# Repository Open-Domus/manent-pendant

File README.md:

# Manent pendant: hardware

Hardware design of the Manent pendant: a jewel on a chain that listens for speech around
its wearer, records it, and hands it to the phone over Bluetooth LE. An oval cabochon of
coloured glass in a titanium rim, 40 x 26 mm, whose stone glows while it listens. The stone
and its light come in red, green or blue, chosen at order.
It is the band of `manent-band` in another form: the same circuit, net for net, in a case
made to be looked at. Firmware and radio protocol live in the `mnemo-band` repository.

Public page: [manentlabs.it/en/pendant/](https://manentlabs.it/en/pendant/) (English), [manentlabs.it/pendente/](https://manentlabs.it/pendente/) (Italian).

Nothing here has been built or measured. This is a first design on paper, checked by
scripts, and several of its choices still wait for the project owner.

| What | Where |
| --- | --- |
| Design document: the jewel, requirements, decisions | [docs/design.md](docs/design.md) |
| Does it fit? Case, layers, cell, board area | [docs/space-budget.md](docs/space-budget.md) |
| How long does it last? | [docs/power-budget.md](docs/power-budget.md) |
| What is undecided or unknown, and what would settle it | [docs/open-questions.md](docs/open-questions.md) |
| Parts with sizes and how far each is verified | [parts/parts.yaml](parts/parts.yaml) |
| Circuit, as data | [electrical/gen/design.py](electrical/gen/design.py) |
| Schematic (KiCad 10), PDF, bill of materials | `electrical/kicad/`, `electrical/out/` |
| Board: an ellipse, placed and routed by scripts, not reviewed | `electrical/kicad/pendant.kicad_pcb`, `electrical/out/board-*.svg` |
| Fit model, drawings, STEP | `mechanical/`, `mechanical/out/` |

## Build

Needs `uv`, and either KiCad 10 or Docker (`docker pull kicad/kicad:10.0`).

```
make all        # schematic, board, checks, tests, fit report, drawings, budgets, STEP
make test       # tests only
make route      # draw the tracks again with Freerouting (needs Java and its jar; see tools/route.sh)
```

The schematic and the board are generated: edit `electrical/gen/design.py` and the fit
model, never the `.kicad_sch` or `.kicad_pcb` files.
Every pin carries a label with its net name instead of drawn wires. `make schematic` runs
KiCad's rule check and compares the netlist KiCad reads with the one in `design.py`.

The board is placed and routed by scripts and passes KiCad's checks, but nobody has reviewed
it: see "Board" in the design document before taking it for more than it is. The tracks
are kept in `electrical/kicad/pendant.ses`; when the placement changes, `make route` draws
them again.

## What it shares with the band

The circuit (`electrical/gen/design.py` differs from the band's only in the switch and in
its notes), the pin tables in `parts/pins`, the checks, the power budget's inputs and the
build scripts. A change to the circuit belongs in both repositories.

## Licences

As for the ring and the band: hardware under CERN-OHL-S v2 (`LICENSE`), documents under
CC BY-SA 4.0 (`LICENSE-docs`). The licence of the scripts is not decided.

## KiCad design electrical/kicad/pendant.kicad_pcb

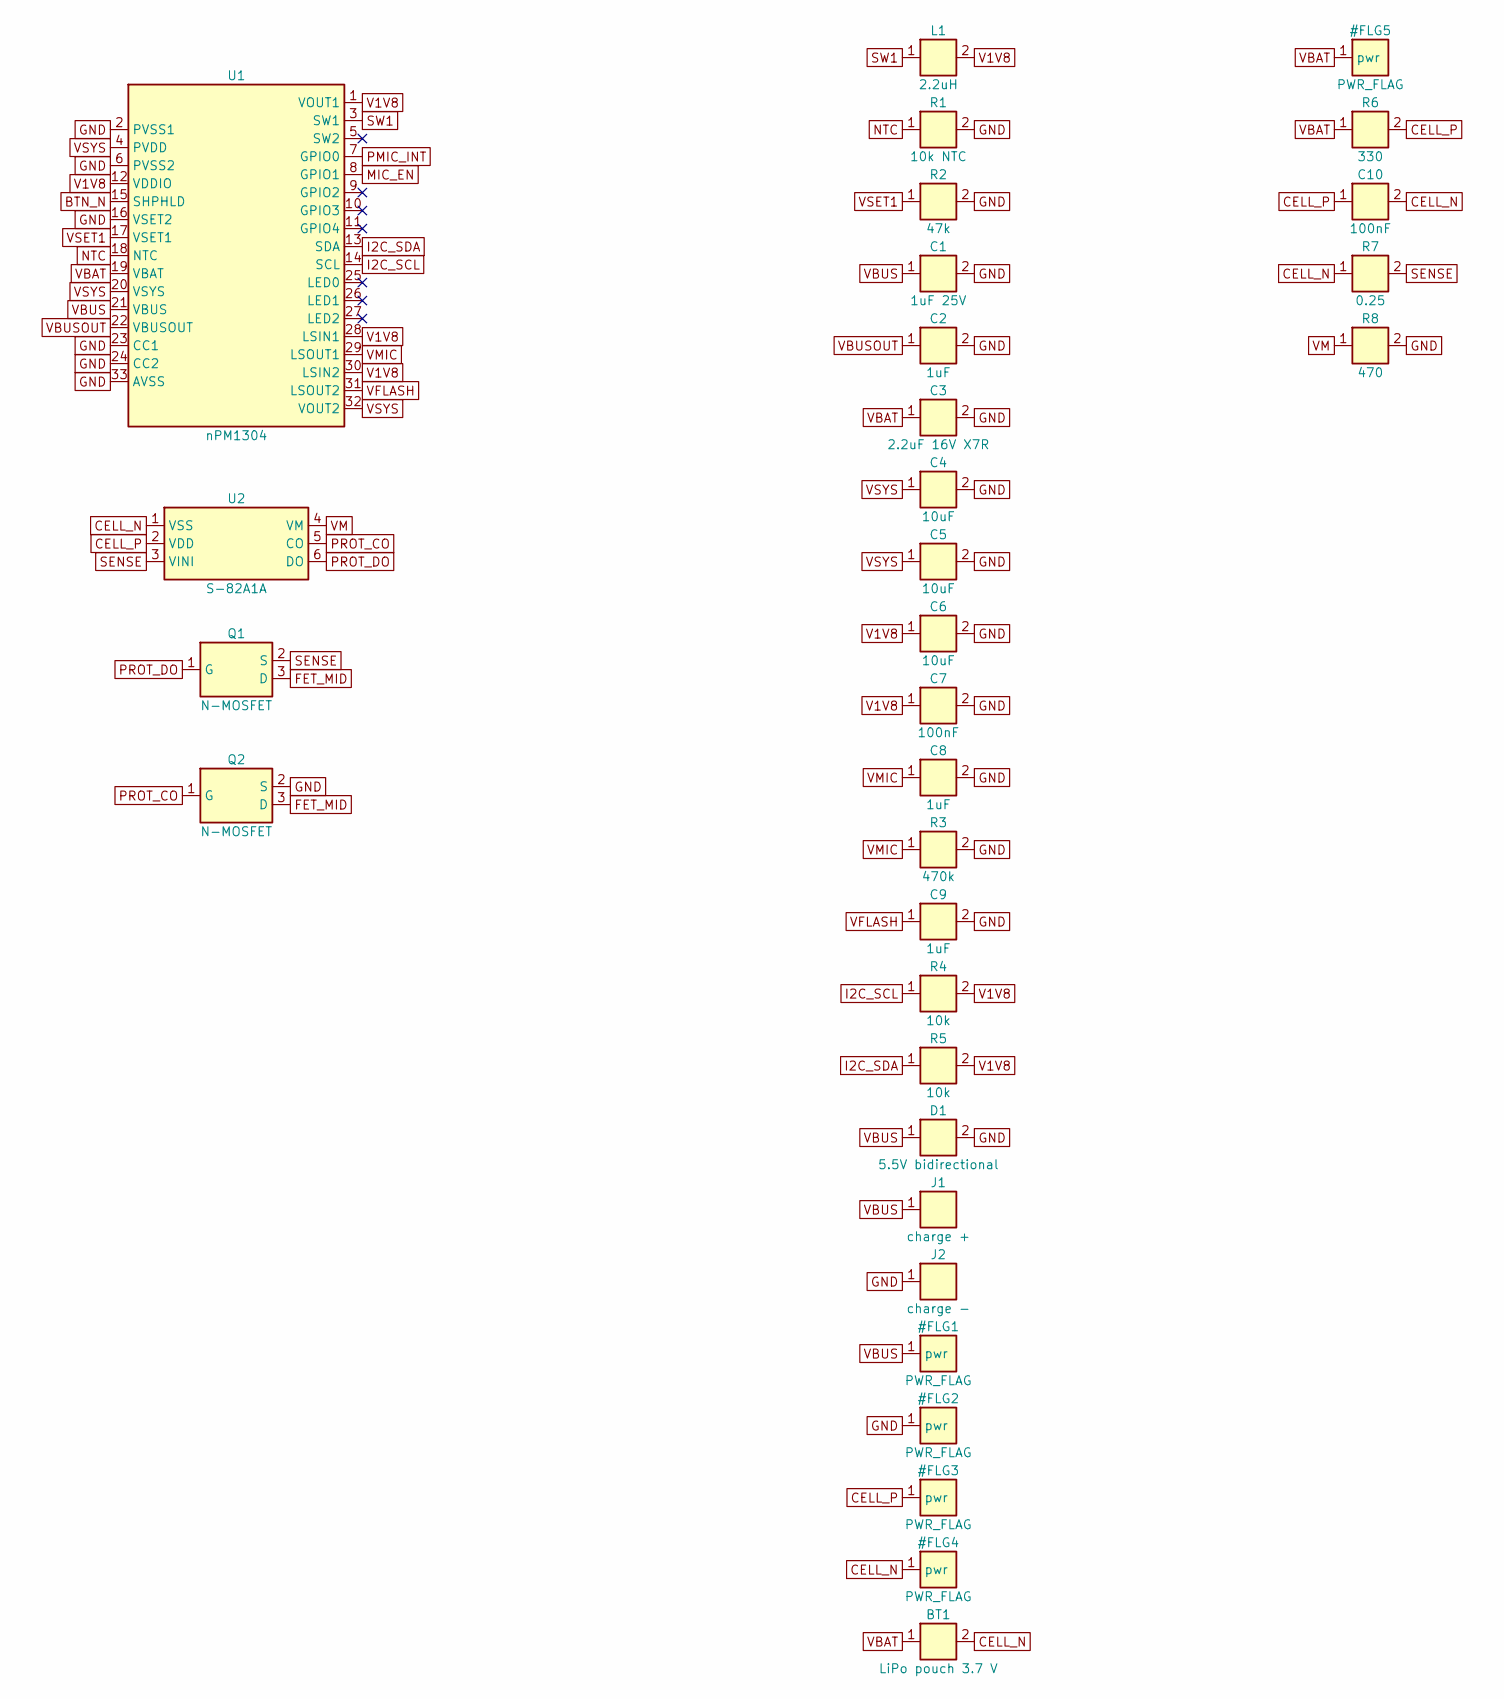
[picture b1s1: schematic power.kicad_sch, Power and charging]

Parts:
BT1: LiPo pouch 3.7 V; Cell_Tabs; MPN 401525 class
C1: 1uF 25V; C_0603_1608Metric
C2, C8, C9: 1uF; C_0402_1005Metric
C3: 2.2uF 16V X7R; C_0603_1608Metric
C4, C5, C6: 10uF; C_0603_1608Metric
C7, C10: 100nF; C_0402_1005Metric
D1: 5.5V bidirectional; D_0201_0603Metric; MPN ESD230-B1-W0201
J1: charge +; Spring_Contact; MPN to choose
J2: charge -; Spring_Contact; MPN to choose
L1: 2.2uH; L_0805_2012Metric; MPN VLS201610HBX-2R2M-1
Q1, Q2: N-MOSFET; SOT-883; MPN PMZB290UNE2
R1: 10k NTC; R_0402_1005Metric; MPN to choose
R2: 47k; R_0402_1005Metric
R3: 470k; R_0402_1005Metric
R4, R5: 10k; R_0402_1005Metric
R6: 330; R_0402_1005Metric
R7: 0.25; R_0402_1005Metric
R8: 470; R_0402_1005Metric
U1: nPM1304; QFN-32-1EP_5x5mm_P0.5mm_EP3.45x3.45mm; MPN nPM1304-QEAA-R7
U2: S-82A1A; DFN-6_1414; MPN S-82A1AAG-A6T5S (variant to confirm)

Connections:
BTN_N: U1.15 (SHPHLD); also elsewhere on the board
CELL_N: BT1.2, C10.2, R7.1, U2.1 (VSS)
CELL_P: C10.1, R6.2, U2.2 (VDD)
FET_MID: Q1.3 (D), Q2.3 (D)
GND: C1.2, C2.2, C3.2, C4.2, C5.2, C6.2, C7.2, C8.2, C9.2, D1.2, J2.1, Q2.2 (S), R1.2, R2.2, R3.2, R8.2, U1.2 (PVSS1), U1.6 (PVSS2), U1.16 (VSET2), U1.23 (CC1), U1.24 (CC2), U1.33 (AVSS); also elsewhere on the board
I2C_SCL: R4.1, U1.14 (SCL); also elsewhere on the board
I2C_SDA: R5.1, U1.13 (SDA); also elsewhere on the board
MIC_EN: U1.8 (GPIO1); also elsewhere on the board
NTC: R1.1, U1.18 (NTC)
PMIC_INT: U1.7 (GPIO0); also elsewhere on the board
PROT_CO: Q2.1 (G), U2.5 (CO)
PROT_DO: Q1.1 (G), U2.6 (DO)
SENSE: Q1.2 (S), R7.2, U2.3 (VINI)
SW1: L1.1, U1.3 (SW1)
V1V8: C6.1, C7.1, L1.2, R4.2, R5.2, U1.1 (VOUT1), U1.12 (VDDIO), U1.28 (LSIN1), U1.30 (LSIN2); also elsewhere on the board
VBAT: BT1.1, C3.1, R6.1, U1.19 (VBAT); also elsewhere on the board
VBUS: C1.1, D1.1, J1.1, U1.21 (VBUS); also elsewhere on the board
VBUSOUT: C2.1, U1.22 (VBUSOUT)
VFLASH: C9.1, U1.31 (LSOUT2); also elsewhere on the board
VM: R8.1, U2.4 (VM)
VMIC: C8.1, R3.1, U1.29 (LSOUT1); also elsewhere on the board
VSET1: R2.1, U1.17 (VSET1)
VSYS: C4.1, C5.1, U1.4 (PVDD), U1.20 (VSYS), U1.32 (VOUT2); also elsewhere on the board

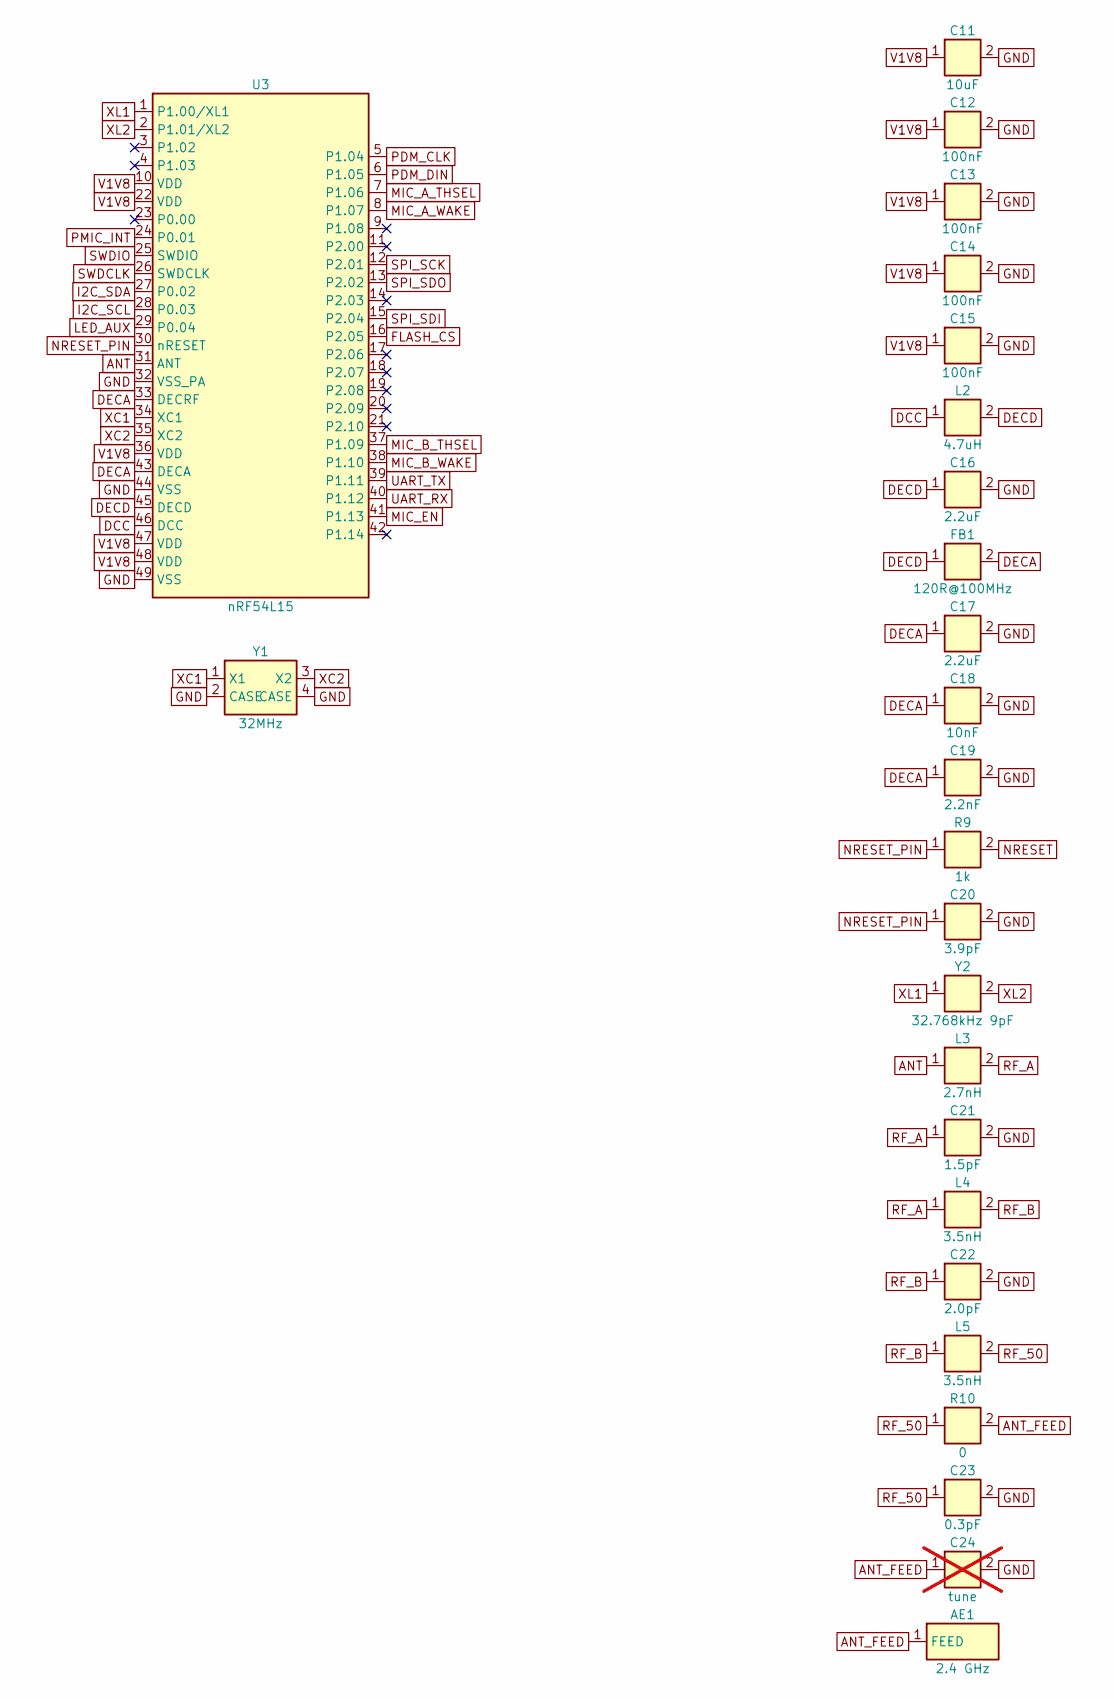
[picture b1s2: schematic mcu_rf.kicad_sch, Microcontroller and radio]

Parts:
AE1: 2.4 GHz; Antenna_1608; MPN ANT1608LL14R2400A
C11: 10uF; C_0603_1608Metric
C12, C13, C14, C15: 100nF; C_0201_0603Metric
C16, C17: 2.2uF; C_0201_0603Metric
C18: 10nF; C_0201_0603Metric
C19: 2.2nF; C_0201_0603Metric
C20: 3.9pF; C_0201_0603Metric
C21: 1.5pF; C_0201_0603Metric; MPN GJM0335C1E1R5WB01
C22: 2.0pF; C_0201_0603Metric; MPN GJM0335C1E2R0WB01
C23: 0.3pF; C_0201_0603Metric
C24: tune; C_0201_0603Metric; not fitted
FB1: 120R@100MHz; L_0201_0603Metric; MPN BLM03AG121SN1D
L2: 4.7uH; L_0402_1005Metric; MPN PLEA67BCA4R7M-1PT00
L3: 2.7nH; L_0201_0603Metric; MPN LQP03HQ2N7B02
L4, L5: 3.5nH; L_0201_0603Metric; MPN LQP03HQ3N5B02
R9: 1k; R_0201_0603Metric
R10: 0; R_0201_0603Metric
U3: nRF54L15; QFN-48-1EP_6x6mm_P0.4mm_EP4.6x4.6mm; MPN nRF54L15-QFAA-R
Y1: 32MHz; Crystal_SMD_2016-4Pin_2.0x1.6mm; MPN CX2016DB32000D0FLJCC
Y2: 32.768kHz 9pF; Crystal_SMD_2012-2Pin_2.0x1.2mm; MPN 9HT11-32.768KDZC-T

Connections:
ANT: L3.1, U3.31 (ANT)
ANT_FEED: AE1.1, C24.1, R10.2
DCC: L2.1, U3.46 (DCC)
DECA: C17.1, C18.1, C19.1, FB1.2, U3.33 (DECRF), U3.43 (DECA)
DECD: C16.1, FB1.1, L2.2, U3.45 (DECD)
FLASH_CS: U3.16 (P2.05); also elsewhere on the board
GND: C11.2, C12.2, C13.2, C14.2, C15.2, C16.2, C17.2, C18.2, C19.2, C20.2, C21.2, C22.2, C23.2, C24.2, U3.32 (VSS_PA), U3.44 (VSS), U3.49 (VSS), Y1.2 (CASE), Y1.4 (CASE); also elsewhere on the board
I2C_SCL: U3.28 (P0.03); also elsewhere on the board
I2C_SDA: U3.27 (P0.02); also elsewhere on the board
LED_AUX: U3.29 (P0.04); also elsewhere on the board
MIC_A_THSEL: U3.7 (P1.06); also elsewhere on the board
MIC_A_WAKE: U3.8 (P1.07); also elsewhere on the board
MIC_B_THSEL: U3.37 (P1.09); also elsewhere on the board
MIC_B_WAKE: U3.38 (P1.10); also elsewhere on the board
MIC_EN: U3.41 (P1.13); also elsewhere on the board
NRESET: R9.2; also elsewhere on the board
NRESET_PIN: C20.1, R9.1, U3.30 (nRESET)
PDM_CLK: U3.5 (P1.04); also elsewhere on the board
PDM_DIN: U3.6 (P1.05); also elsewhere on the board
PMIC_INT: U3.24 (P0.01); also elsewhere on the board
RF_50: C23.1, L5.2, R10.1
RF_A: C21.1, L3.2, L4.1
RF_B: C22.1, L4.2, L5.1
SPI_SCK: U3.12 (P2.01); also elsewhere on the board
SPI_SDI: U3.15 (P2.04); also elsewhere on the board
SPI_SDO: U3.13 (P2.02); also elsewhere on the board
SWDCLK: U3.26 (SWDCLK); also elsewhere on the board
SWDIO: U3.25 (SWDIO); also elsewhere on the board
UART_RX: U3.40 (P1.12); also elsewhere on the board
UART_TX: U3.39 (P1.11); also elsewhere on the board
V1V8: C11.1, C12.1, C13.1, C14.1, C15.1, U3.10 (VDD), U3.22 (VDD), U3.36 (VDD), U3.47 (VDD), U3.48 (VDD); also elsewhere on the board
XC1: U3.34 (XC1), Y1.1 (X1)
XC2: U3.35 (XC2), Y1.3 (X2)
XL1: U3.1 (P1.00/XL1), Y2.1
XL2: U3.2 (P1.01/XL2), Y2.2

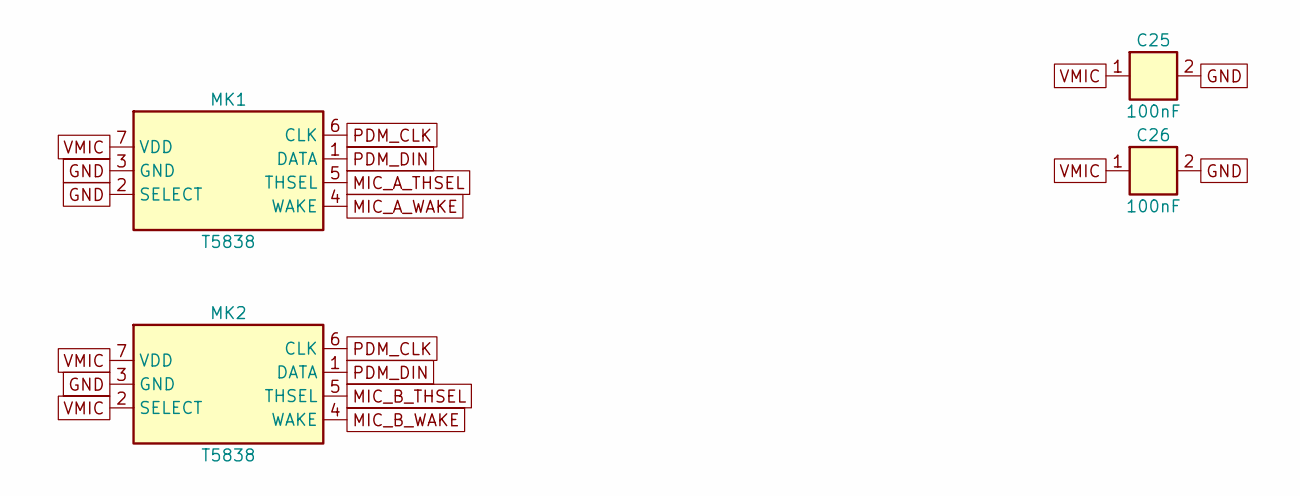
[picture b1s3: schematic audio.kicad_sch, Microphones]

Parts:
C25, C26: 100nF; C_0201_0603Metric
MK1, MK2: T5838; MPN MMICT5838-00-012

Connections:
GND: C25.2, C26.2, MK1.2 (SELECT), MK1.3 (GND), MK2.3 (GND); also elsewhere on the board
MIC_A_THSEL: MK1.5 (THSEL); also elsewhere on the board
MIC_A_WAKE: MK1.4 (WAKE); also elsewhere on the board
MIC_B_THSEL: MK2.5 (THSEL); also elsewhere on the board
MIC_B_WAKE: MK2.4 (WAKE); also elsewhere on the board
PDM_CLK: MK1.6 (CLK), MK2.6 (CLK); also elsewhere on the board
PDM_DIN: MK1.1 (DATA), MK2.1 (DATA); also elsewhere on the board
VMIC: C25.1, C26.1, MK1.7 (VDD), MK2.2 (SELECT), MK2.7 (VDD); also elsewhere on the board

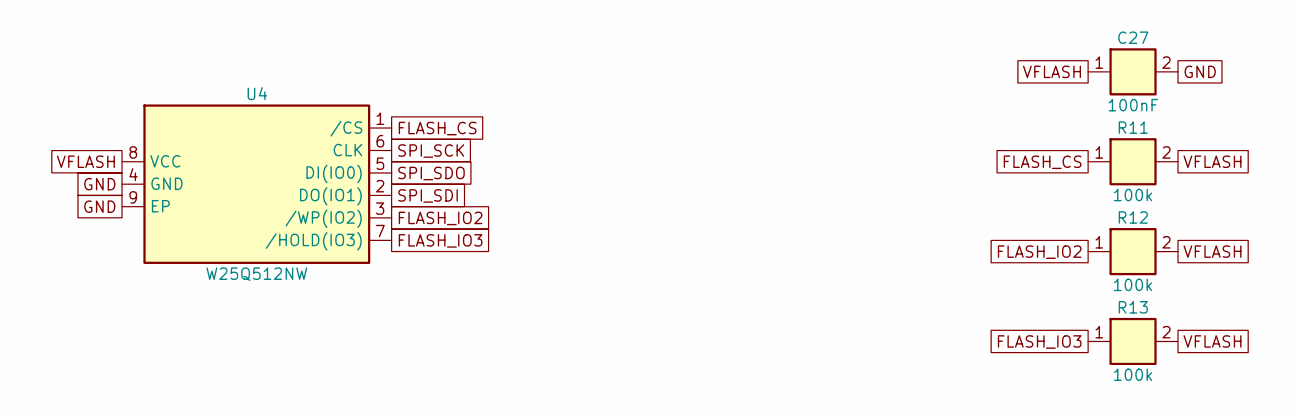
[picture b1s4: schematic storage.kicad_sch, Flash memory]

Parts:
C27: 100nF; C_0402_1005Metric
R11, R12, R13: 100k; R_0402_1005Metric
U4: W25Q512NW; WSON-8-1EP_8x6mm_P1.27mm_EP3.4x4.3mm; MPN W25Q512NW (ordering code to confirm)

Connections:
FLASH_CS: R11.1, U4.1 (/CS); also elsewhere on the board
FLASH_IO2: R12.1, U4.3 (/WP(IO2))
FLASH_IO3: R13.1, U4.7 (/HOLD(IO3))
GND: C27.2, U4.4 (GND), U4.9 (EP); also elsewhere on the board
SPI_SCK: U4.6 (CLK); also elsewhere on the board
SPI_SDI: U4.2 (DO(IO1)); also elsewhere on the board
SPI_SDO: U4.5 (DI(IO0)); also elsewhere on the board
VFLASH: C27.1, R11.2, R12.2, R13.2, U4.8 (VCC); also elsewhere on the board

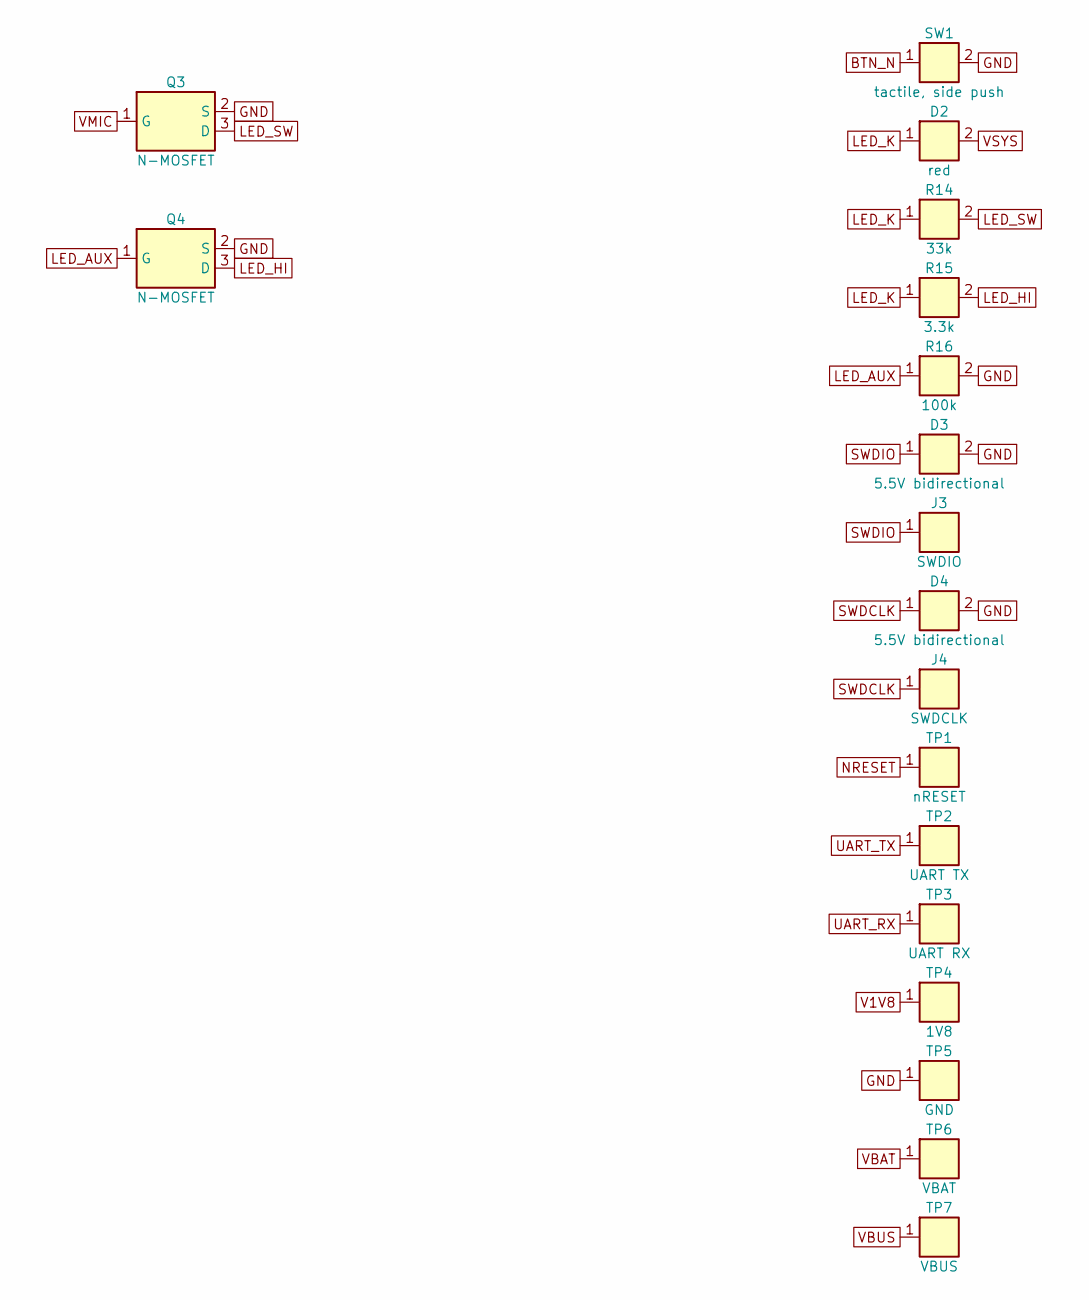
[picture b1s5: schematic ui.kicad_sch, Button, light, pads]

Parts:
D2: red; LED_0402_1005Metric; MPN SML-P11VT
D3, D4: 5.5V bidirectional; D_0201_0603Metric; MPN ESD230-B1-W0201
J3: SWDIO; Spring_Contact; MPN to choose
J4: SWDCLK; Spring_Contact; MPN to choose
Q3, Q4: N-MOSFET; SOT-883; MPN PMZB290UNE2
R14: 33k; R_0402_1005Metric
R15: 3.3k; R_0402_1005Metric
R16: 100k; R_0402_1005Metric
SW1: tactile, side push; EVQP7J; MPN EVQP7J01P
TP1: nRESET; Pad_Test_D1.0
TP2: UART TX; Pad_Test_D1.0
TP3: UART RX; Pad_Test_D1.0
TP4: 1V8; Pad_Test_D1.0
TP5: GND; Pad_Test_D1.0
TP6: VBAT; Pad_Test_D1.0
TP7: VBUS; Pad_Test_D1.0

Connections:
BTN_N: SW1.1; also elsewhere on the board
GND: D3.2, D4.2, Q3.2 (S), Q4.2 (S), R16.2, SW1.2, TP5.1; also elsewhere on the board
LED_AUX: Q4.1 (G), R16.1; also elsewhere on the board
LED_HI: Q4.3 (D), R15.2
LED_K: D2.1, R14.1, R15.1
LED_SW: Q3.3 (D), R14.2
NRESET: TP1.1; also elsewhere on the board
SWDCLK: D4.1, J4.1; also elsewhere on the board
SWDIO: D3.1, J3.1; also elsewhere on the board
UART_RX: TP3.1; also elsewhere on the board
UART_TX: TP2.1; also elsewhere on the board
V1V8: TP4.1; also elsewhere on the board
VBAT: TP6.1; also elsewhere on the board
VBUS: TP7.1; also elsewhere on the board
VMIC: Q3.1 (G); also elsewhere on the board
VSYS: D2.2; also elsewhere on the board

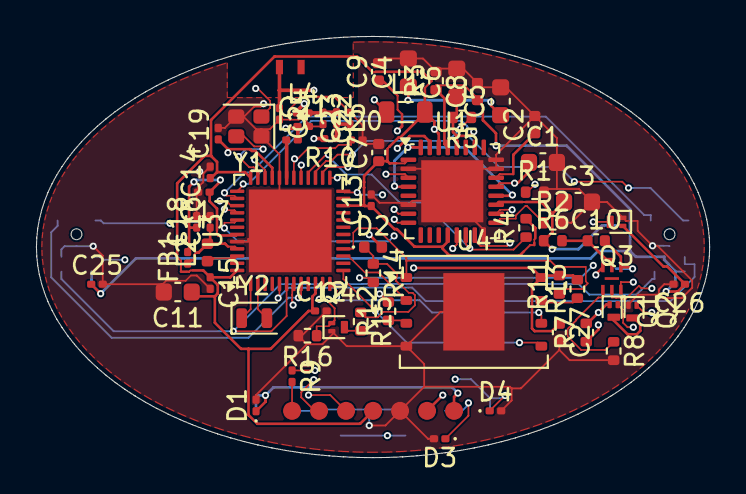
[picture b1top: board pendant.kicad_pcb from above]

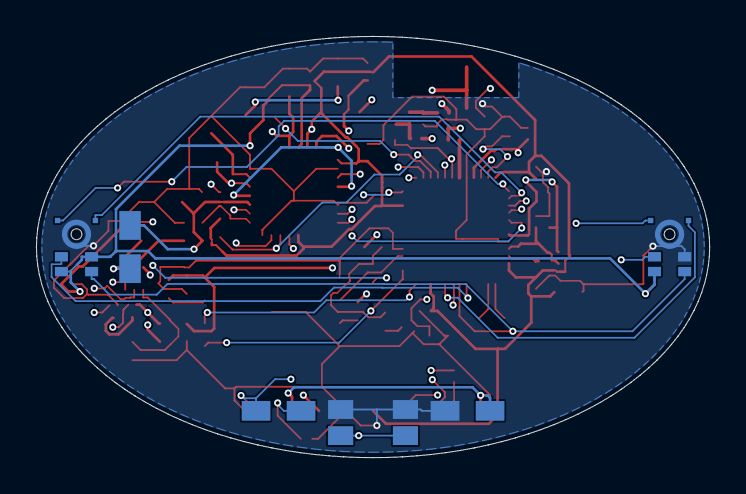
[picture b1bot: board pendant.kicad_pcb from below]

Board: 4 copper layers, 37.4 x 23.4 mm, 79 parts (8 on the bottom side), 57 nets.

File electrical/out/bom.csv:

References,Quantity,Value,Manufacturer,Part number,Package,Fitted,Notes
U1,1,nPM1304,Nordic Semiconductor,nPM1304-QEAA-R7,"QFN-32 5x5, 0.5 mm pitch",yes,"Charges at up to 100 mA: enough for these cells. BUCK2 unused as in Nordic's reference configuration 2: VSET2 grounded, SW2 open, VOUT2 to VSYS. LED0-2, GPIO2-4 left open"
L1,1,2.2uH,TDK,VLS201610HBX-2R2M-1,0806,yes,"Nordic asks for DCR under 0.4 ohm in 0806 (2.0 x 1.6 mm); this one is 0.17 max, 1.45 A, 1.0 tall. The same part on the band, the card and the pendant"
R1,1,10k NTC,,to choose,0402,yes,"Thermistor, B about 3380 K, against the cell: stops the charge when the closed case is too warm or too cold"
R2,1,47k,,,0402,yes,Sets BUCK1 to 1.8 V at power-on
C1,1,1uF 25V,,,0603,yes,"As Nordic's nPM1304-QEAA reference layout 1.0, configuration 2"
C2 C8 C9,3,1uF,,,0402,yes,"As Nordic's nPM1304-QEAA reference layout 1.0, configuration 2 | Load switch output. As Nordic's nPM1304-QEAA reference layout 1.0, configuration 2"
C3,1,2.2uF 16V X7R,,,0603,yes,"As Nordic's nPM1304-QEAA reference layout 1.0, configuration 2 (Taiyo Yuden EMK107BB7225KA-T there)"
C4 C5 C6 C11,4,10uF,,,0603,yes,"Buck input, at PVDD and PVSS1. As Nordic's nPM1304-QEAA reference layout 1.0, configuration 2 | VSYS output. As Nordic's nPM1304-QEAA reference layout 1.0, configuration 2 | Buck output: at least 4 uF effective. As Nordic's nPM1304-QEAA reference layout 1.0, configuration 2"
C7 C10 C27,3,100nF,,,0402,yes,VDDIO
R3,1,470k,,,0402,yes,"Empties the rail when the load switch opens, so a mute puts the light out at once, as on the ring and the card"
R4 R5,2,10k,,,0402,yes,
D1 D3 D4,3,5.5V bidirectional,Infineon,ESD230-B1-W0201,0201,yes,"The pad is on the outside of the closed case, against the skin: protected as on the card"
J1,1,charge +,,to choose,spring contact,yes,To a pad on the back cover. The bail lets the pendant into its dock one way only
J2,1,charge -,,to choose,spring contact,yes,
BT1,1,LiPo pouch 3.7 V,to choose,401525 class,,yes,Size and capacity depend on the case; see docs/space-budget.md
R6,1,330,,,0402,yes,Protector supply filter
U2,1,S-82A1A,ABLIC,S-82A1AAG-A6T5S (variant to confirm),DFN-6 1.4x1.4,yes,Fit only if the cell has no protection of its own; thresholds to match the charge voltage
R7,1,0.25,,,0402,yes,"Overcurrent sense: about 200 mA trip (calculated, not from a datasheet)"
R8,1,470,,,0402,yes,
Q1 Q2 Q3 Q4,4,N-MOSFET,Nexperia,PMZB290UNE2,DFN1006B-3,yes,"Discharge FET; two singles with their drains joined. The same FET in all eight places of the four products | Charge FET | Gate is the microphone rail: the light is on whenever the microphones have power. Vgs(th) under 1 V | Firmware can only add light, never remove the steady glow"
U3,1,nRF54L15,Nordic Semiconductor,nRF54L15-QFAA-R,"QFN-48 6x6, 0.4 mm pitch",yes,Pin 49 is the exposed pad: ground
C12 C13 C14 C15 C25 C26,6,100nF,,,0201,yes,"One next to each side's VDD pin. As Nordic's nRF54L15-QFAA reference layout 0.8 | X7R, next to pin 7 of microphone A | X7R, next to pin 7 of microphone B"
L2,1,4.7uH,TDK,PLEA67BCA4R7M-1PT00,0402,yes,"DC/DC inductor, the ring's part. Nordic's QFN reference takes a 0603 of 0.65 ohm and 120 mA; this one is 1.08 ohm max"
C16 C17,2,2.2uF,,,0201,yes,As Nordic's nRF54L15-QFAA reference layout 0.8
FB1,1,120R@100MHz,Murata,BLM03AG121SN1D,0201,yes,"The reference asks 120 ohm at 100 MHz, 200 mA, 0.5 ohm max: the ring's part"
C18,1,10nF,,,0201,yes,As Nordic's nRF54L15-QFAA reference layout 0.8
C19,1,2.2nF,,,0201,yes,X7R. As Nordic's nRF54L15-QFAA reference layout 0.8
R9,1,1k,,,0201,yes,"Filter on the reset pin, next to the antenna pin. As Nordic's nRF54L15-QFAA reference layout 0.8"
C20,1,3.9pF,,,0201,yes,"C0G, at the reset pin. As Nordic's nRF54L15-QFAA reference layout 0.8"
Y1,1,32MHz,Kyocera,CX2016DB32000D0FLJCC,2016,yes,"2.0 x 1.6 mm, 8 pF, 10 ppm, as the reference asks (8 pF, 40 ppm in all); pads 2 and 4 are the lid, grounded: check against its drawing. Load capacitors are inside the chip"
Y2,1,32.768kHz 9pF,TXC,9HT11-32.768KDZC-T,2012,yes,"Fitted, as on the band: the pendant stays connected for days and there is room. Load capacitors are inside the chip"
L3,1,2.7nH,Murata,LQP03HQ2N7B02,0201,yes,Matching network. As Nordic's nRF54L15-QFAA reference layout 0.8
C21,1,1.5pF,Murata,GJM0335C1E1R5WB01,0201,yes,Matching network. As Nordic's nRF54L15-QFAA reference layout 0.8
L4 L5,2,3.5nH,Murata,LQP03HQ3N5B02,0201,yes,Matching network. As Nordic's nRF54L15-QFAA reference layout 0.8
C22,1,2.0pF,Murata,GJM0335C1E2R0WB01,0201,yes,Matching network. As Nordic's nRF54L15-QFAA reference layout 0.8
R10,1,0,,,0201,yes,"Antenna tuning, series: value from measurement in a closed case, inside its metal rim, on a chest"
C23,1,0.3pF,,,0201,yes,"C0G, 0.1 pF tolerance: the last part of the matching network. As Nordic's nRF54L15-QFAA reference layout 0.8"
C24,1,tune,,,0201,no,"Antenna tuning, shunt"
AE1,1,2.4 GHz,Yageo,ANT1608LL14R2400A,1608 chip antenna,yes,Chip antenna or printed trace at the edge of the board; decided with the first radio measurements
MK1 MK2,2,T5838,TDK InvenSense,MMICT5838-00-012,3.5x2.65x0.98 bottom port,yes,"Microphone A, at the tip with the bail, towards the mouth; SELECT at GND picks its clock edge. No pull resistor on DATA. Board hole 0.5-1.0 mm under the port | Microphone B, at the opposite tip; SELECT at VMIC picks its clock edge. No pull resistor on DATA. Board hole 0.5-1.0 mm under the port"
U4,1,W25Q512NW,Winbond,W25Q512NW (ordering code to confirm),WSON-8 8x6,yes,"512 Mbit at 1.8 V; part number and package from memory, not from the datasheet. Exposed pad to ground is the usual practice, to confirm. Any 1.8 V serial NOR in this package fits"
R11 R12 R13 R16,4,100k,,,0402,yes,Keeps the chip deselected while the rail rises | Termination in single-bit SPI to confirm | Bright light off while the SoC is in reset
SW1,1,"tactile, side push",Panasonic,EVQP7J01P,side-push 3.5x2.9x1.35,yes,"The card's switch. Under the board, at its edge: a pusher in the rim presses it. Pulled up inside the PMIC (SHPHLD). The SoC learns of presses from the PMIC interrupt, as on the ring"
D2,1,red,Rohm,SML-P11VT,1.0x0.6x0.2,yes,"Pin 1 is the cathode. Under the stone: it lights the whole cabochon from inside. This is the red one; the green and blue pendants take an LED of their colour in the same package, to choose"
R14,1,33k,,,0402,yes,"Steady glow, about 0.05 mA, whenever the microphones have power; adjust after a look through the stone, for each colour"
R15,1,3.3k,,,0402,yes,"Bright, about 0.5 mA: firmware turns it on while sound is being recorded"
J3,1,SWDIO,,to choose,spring contact,yes,Service pad on the back cover: reachable with the case closed
J4,1,SWDCLK,,to choose,spring contact,yes,Service pad on the back cover: reachable with the case closed

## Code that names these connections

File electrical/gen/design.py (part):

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TVS = two_pin("TVS", "D")
PAD = SymDef("PAD", "TP", (Pin("1", "~", "passive", "L"),), width=5.08)
CONTACT = SymDef("CONTACT", "J", (Pin("1", "~", "passive", "L"),), width=5.08)
ANT = SymDef("ANTENNA", "AE", (Pin("1", "FEED", "passive", "L"),), width=10.16)
FLAG = SymDef("PWR_FLAG", "#FLG", (Pin("1", "pwr", "power_out", "L"),), width=5.08, virtual=True)
NFET = ic("NMOS", "Q", "1 G i L\n2 S p R\n3 D p R", width=10.16)

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4 PVDD pi L
5 SW2 p R
6 PVSS2 pi L
7 GPIO0 b R
8 GPIO1 b R
9 GPIO2 b R
10 GPIO3 b R
11 GPIO4 b R
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        "VSYS": "VSYS", "PVDD": "VSYS", "VDDIO": "V1V8", "AVSS": "GND", "PVSS1": "GND", "PVSS2": "GND",
        "VSET1": "VSET1", "VSET2": "GND", "SHPHLD": "BTN_N", "SW1": "SW1", "VOUT1": "V1V8",
        "VOUT2": "VSYS", "LSIN1": "V1V8", "LSOUT1": "VMIC", "LSIN2": "V1V8", "LSOUT2": "VFLASH",
        "SCL": "I2C_SCL", "SDA": "I2C_SDA", "GPIO0": "PMIC_INT", "GPIO1": "MIC_EN",
    }), mpn="nPM1304-QEAA-R7", mfr="Nordic Semiconductor", package="QFN-32 5x5, 0.5 mm pitch",
        note="Charges at up to 100 mA: enough for these cells. "
             "BUCK2 unused as in Nordic's reference configuration 2: VSET2 grounded, SW2 open, VOUT2 to VSYS. "
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    add(SOC, "nRF54L15", "mcu_rf", by_name(SOC, {
        "VDD": "V1V8", "DCC": "DCC", "DECD": "DECD", "DECA": "DECA", "DECRF": "DECA",
        "VSS": "GND", "VSS_PA": "GND", "XC1": "XC1", "XC2": "XC2", "ANT": "ANT",
        "nRESET": "NRESET_PIN", "SWDCLK": "SWDCLK", "SWDIO": "SWDIO", **SOC_NETS,
    }), mpn="nRF54L15-QFAA-R", mfr="Nordic Semiconductor", package="QFN-48 6x6, 0.4 mm pitch",
        note="Pin 49 is the exposed pad: ground")
    cap("10uF", "V1V8", "mcu_rf", pkg="0603")
    for _ in range(4):
        cap("100nF", "V1V8", "mcu_rf", pkg="0201", note="One next to each side's VDD pin. " + REF)
    add(L, "4.7uH", "mcu_rf", ("DCC", "DECD"), mpn="PLEA67BCA4R7M-1PT00", mfr="TDK", package="0402",
        note="DC/DC inductor, the ring's part. Nordic's QFN reference takes a 0603 of 0.65 ohm and 120 mA; this one is 1.08 ohm max")
    cap("2.2uF", "DECD", "mcu_rf", pkg="0201", note=REF)
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    cap("2.2uF", "DECA", "mcu_rf", pkg="0201", note=REF)
    cap("10nF", "DECA", "mcu_rf", pkg="0201", note=REF)
    cap("2.2nF", "DECA", "mcu_rf", pkg="0201", note="X7R. " + REF)
    res("1k", "NRESET_PIN", "NRESET", "mcu_rf", pkg="0201", note="Filter on the reset pin, next to the antenna pin. " + REF)
    cap("3.9pF", "NRESET_PIN", "mcu_rf", pkg="0201", note="C0G, at the reset pin. " + REF)
    add(XTAL4, "32MHz", "mcu_rf", {"1": "XC1", "3": "XC2", "2": "GND", "4": "GND"}, mpn="CX2016DB32000D0FLJCC", mfr="Kyocera", package="2016",
        note="2.0 x 1.6 mm, 8 pF, 10 ppm, as the reference asks (8 pF, 40 ppm in all); pads 2 and 4 are the lid, grounded: check against its drawing. "
             "Load capacitors are inside the chip")
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            mpn="MMICT5838-00-012", mfr="TDK InvenSense", package="3.5x2.65x0.98 bottom port",
            note=f"Microphone {name}, at {where}; SELECT at {select} picks its clock edge. "
                 "No pull resistor on DATA. Board hole 0.5-1.0 mm under the port")
        cap("100nF", "VMIC", "audio", pkg="0201", note=f"X7R, next to pin 7 of microphone {name}")

    # ---- flash ---------------------------------------------------------------------------
    add(FLASH, "W25Q512NW", "storage", by_name(FLASH, {
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    add(NFET, "N-MOSFET", "ui", {"1": "LED_AUX", "2": "GND", "3": "LED_HI"}, mpn="PMZB290UNE2", mfr="Nexperia", package="DFN1006B-3",
        note="Firmware can only add light, never remove the steady glow")
    res("100k", "LED_AUX", "GND", "ui", note="Bright light off while the SoC is in reset")
    for label, net in (("SWDIO", "SWDIO"), ("SWDCLK", "SWDCLK")):
        add(TVS, "5.5V bidirectional", "ui", (net, "GND"), mpn="ESD230-B1-W0201", mfr="Infineon", package="0201",
            note="The pad is on the outside of the closed case, against the skin: protected as on the card")
        add(CONTACT, label, "ui", (net,), mpn="to choose", package="spring contact",
            note="Service pad on the back cover: reachable with the case closed")
    for label, net in (("nRESET", "NRESET"), ("UART TX", "UART_TX"), ("UART RX", "UART_RX"), ("1V8", "V1V8"),
                       ("GND", "GND"), ("VBAT", "VBAT"), ("VBUS", "VBUS")):
        add(PAD, label, "ui", (net,), note="Test pad on the board, for the factory test before the case is closed")
    for c in comps:
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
